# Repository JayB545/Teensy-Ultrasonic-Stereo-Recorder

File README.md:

# TUFR 4.2 - Teensy Ultrasonic Field Recorder

Firmware 4.2, build 2026-11-14b.

Low-power field recorder for ultrasonic sound (bats, cetaceans). A Teensy 4.1 records 16-bit WAV or lossless FLAC files to a microSD card from a WMXZ-EU ADC_V2 module (TLV320ADC6140): 1, 2 or 4 channels at 48/96/192 kHz, 1-2 channels at 384 kHz, 1 channel at 768 kHz or `-768` (768 kHz sampled, 384 kHz files). Every deployment setting is read from `TUFR_Setup.txt` on the SD card; nothing needs recompiling.

**Users: see the TUFR 4.2 User Manual** for the setup file, filter responses, gain, file formats, scheduling, LED codes and the log. This README is for whoever builds or modifies the firmware.

## Building

- Arduino IDE with Teensyduino, board **Teensy 4.1**, Tools > Optimize **"Faster"**.
- Libraries: **SdFat** (the Teensyduino copy), **Time** (TimeLib), **Wire**. No Snooze library.
- The sketch folder must be named `TUFR_4.2` (Arduino requires the folder to match `TUFR_4.2.ino`).
- RAM: the FLAC encoder reserves about 92 KB of RAM1 even in WAV mode. If the compile reports RAM1 short, build `tufr_flac.c` with `-DTUFR_FLAC_MAX_BLOCK=1024` (files about 0.3 % larger).
- Uploading with the Teensy Loader sets the RTC to the computer's clock.
- Before a field release check that `TUFR_WDT_TEST` is `0`.

## Hardware notes

- MotherBoard: BarlowAGAD TUFR Bridgeboard v3a (the v4 motherboard is in design). Pin assignments are in `TUFR_Config.h` and `TUFR_pin_table.html`: ADC_EN 9, SHDNZ 6, I2C SDA 18 / SCL 19, BCLK 21, LRCLK 20, data 8, shutdown button 2, LED 13, Vin divider 22 (A8). In the current version, components are hand-soldered onto the bare motherboard.
- ADC Module: In the current version, the ADC module is manufactured fully populated (except for the pin headers).
- **IOVD**: the ADC module's IOVD pad must be connected to the Teensy 3.3 V (without it: cold-start dropouts at 384 kHz and HF spikes).
- **USB power**: cut the Teensy's VUSB-VIN pad. USB then carries data only; bench work with the serial monitor needs battery or bench-supply power. `Vin` in the log is then the buck output (about 4.1 V); below about 3.8 V the batteries are running out.
- Input pins must stay within the ADC's supply rails (0 to 3.3 V). Consider a series resistor and clamp diodes per input if a pre-amp runs from a higher supply.

## Compile-time settings

| Setting | Where | Default | What it does |
| --- | --- | --- | --- |
| `TUFR_WATCHDOG` | `TUFR_4.2.ino` | 1 | Hardware watchdog (RTWDOG) on |
| `WDT_TIMEOUT_S` | `TUFR_4.2.ino` | 10 | Watchdog timeout, seconds (bench-confirmed) |
| `TUFR_WDT_TEST` | `TUFR_4.2.ino` | 0 | Bench test: 1 = stop feeding the watchdog 30 s into the first file (runs once; delete `TUFR_WDT_DONE.TXT` to repeat). **0 for the field.** |
| `DEAD_STREAM_RECOVER_MS` | `TUFR_4.2.ino` | 500 | All-zero audio this long = dead stream |
| `DEAD_STREAM_INPLACE_TRIES` | `TUFR_4.2.ino` | 3 | In-place ADC restarts per file before a full power cycle |
| `POWER_CYCLE_SHORT_S`, `_LONG_S`, `_SHORT_TRIES` | `TUFR_4.2.ino` | 60, 600, 3 | Power-off time for recovery: 60 s, then 10 min after three in a row |
| `SD_WRITE_FAIL_RUN` | `TUFR_4.2.ino` | 8 | Consecutive failed SD writes that count as a failing card |
| `TUFR_PREALLOCATE` | `TUFR_4.2.ino` | 0 | Preallocate the next file (off: preallocation caused mid-file misses) |
| `TUFR_USB_OFF` | `TUFR_4.2.ino` | 2 | Power down USB PHY and PLL while recording if no serial monitor is open (saves about 13 mA) |
| `gFiltSel` | `TUFR_4.2.ino` | -1 | ADC decimation filter: -1 auto (linear phase at 384 kHz, ultra-low latency elsewhere), 0 linear, 1 low latency, 2 ultra-low latency. Not in the setup file. |
| `TUFR_HPF_D1_SIGN` | `TUFR_Config.h` | 1 | Sign convention of the programmable high-pass (1 is correct) |
| `TUFR_VIN_DIVIDER` | `TUFR_Config.h` | 2.0 | (Rtop + Rbottom) / Rbottom of the Vin divider on pin 22 |
| `TUFR_FLAC_MAX_BLOCK` | `tufr_flac.h` | 2048 | FLAC frame length per channel |
| `MAX_QUEUE` | `global.h` | 14 | Audio queue, 32 KB slots (about 300 ms at 384 kHz x 2 ch) |

## How it works

- **Capture**: Walter Zimmer's SAI/DMA driver fills a 14-slot queue of 16-bit samples (32 KB per slot); `loop()` writes slots to the card, or encodes them to FLAC first. In `-768` mode a 43-tap half-band FIR in the DMA interrupt halves the rate.
- **Gap-free files**: in continuous mode the next file is opened about 6 s before the join, so only the old file's close (about 25 ms) falls at the join; each file starts at the previous file's scheduled end, so files are exactly the set length. The FLAC encoder carries its state across files.
- **FLAC** (`tufr_flac.c/.h`, written for TUFR, no libFLAC, no malloc): fixed predictors of order 0-4 chosen per channel per frame, partitioned Rice coding (up to 64 partitions), 2048-sample frames, constant/verbatim subframes, a 512-byte header so every 32 KB SD write stays sector-aligned, header rewritten at close. About 33 cycles per sample on quiet input, 40-48 on loud input.
- **Waits** (duty cycle, daily window, scheduled start) use Walter Zimmer's SNVS hibernate: the 3.3 V regulator is switched off (0.75 mA) and the RTC alarm restarts the board; a marker file `TUFR_HIB.TXT` tells the restart it is a wake.
- **Unattended recovery**: nothing but the shutdown button stops the recorder for good.
  1. Dead stream (0.5 s of zeros): up to 3 in-place ADC restarts per file, pauses 0.3, 2 and 10 s.
  2. Full power cycle (hibernate 60 s, then 10 min after three in a row; count reset after a file with 10 s of live audio) when that fails, when the ADC does not answer (5 blinks), or on any SD problem (2 blinks: missing, full, failing writes, file not created). Hibernation also removes IOVD power, which an in-place ADC restart cannot.
  3. Watchdog: a hang of 10 s restarts the chip, which powers off at once (before touching the SD card) for 60-123 s. The wake time is chosen so that the alarm second modulo 64 is 37; the next boot recognises that and logs `WATCHDOG_RESET`. (The SNVS general-purpose registers did not keep a value through the power-off on this board, so they are not used.)
- **SD space**: free space is measured once per boot (`SD_SPACE`) and counted down as files close; a file is started only if a full-size WAV file would fit.
- **Setup file**: ten lines in a fixed order; the file-format line is a word (`WAV`/`FLAC`); if line 4 is a number the format line is treated as missing (WAV). 3 channels are recorded as 4 (16384-sample blocks are not a whole number of 3-channel frames). `-768` with FLAC raises the clock to 100 MHz.

## Files

| File | Role |
| --- | --- |
| `TUFR_4.2.ino` | Main sketch: setup file, file handling, FLAC staging, waits, hibernate, recovery, watchdog |
| `tufr_flac.c/.h` | Lossless FLAC encoder |
| `Teensy.cpp/.h`, `adc.cpp/.h`, `process.h`, `queueProcess.cpp`, `global.h` | Walter Zimmer's capture driver (modifications noted in the sketch header) |
| `adcRuntime.cpp/.h` | ADC configuration, channel count, high-pass, retries, health checks |
| `rtc.h`, `rtcImpl.cpp` | Time functions for the capture driver (never define `rtc_get`/`rtc_set` here; they belong to the Teensy core) |
| `TUFR_Config.h` | Pins, Vin divider, high-pass sign |
| `TUFR_Setup.txt` | Template setup file for the SD card |
| `TUFR_pin_table.html` | Printable pin table |

The PC test harness for the encoder (`TUFR_flac_pc_test`) ships beside this folder.

## Status (2026-11-14)

Bench-validated on Bridgeboard v3:

- WAV and FLAC at 384 kHz x 1 and 2 ch, 192 kHz x 4 ch, `-768`; continuous files joined without gaps; 60 MHz with no mid-file misses, including loud white noise on all channels (worst case 62 % CPU).
- High-pass presets and programmable corners; frequency response at 96, 192, 384 kHz and `-768` (see the manual).
- Setup file 13b format, 3 to 4 channels, `CLOCK_RAISED`.
- Recovery: watchdog restart, power-off and `WATCHDOG_RESET` logging; missing SD card (2 blinks, recording resumes when a card is inserted).
- Hibernate between recordings at 0.75 mA; recording 87 mA at 384 kHz x 2 ch WAV.

### Bench tests still to do

1. Full card: a nearly full card should end with complete files, `CARD_FULL` and 2 blinks.
2. A WAV file cut off by a reset should open in Audacity and PAMGuard (placeholder header "length unknown").
3. Recording current, FLAC vs WAV at 60 MHz and at other rates and channel counts (the manual's battery figures cover only 384 kHz x 2 ch WAV).
4. One recording on the towed array with the 40 dB pre-amp and about 10 dB ADC gain: headroom and FLAC ratio.
5. Recording at 48 kHz (anti-alias response not measured).

### Known open issues

- An input overload (1.5 Vrms) once stopped the ADC's output entirely (seen twice on 2026-11-13, not reproduced since); recovery now covers it.
- Small spikes at 468 Hz and multiples (source unknown), a 32.77 kHz spur (RTC crystal), 60 Hz pickup.
- The first file of a 768 kHz run can lose up to about 1 s to an SD stall at start-up (before the file opens).

## Version history

- **4.2 (2026-11-12 to 11-14)**: optional FLAC; encoder 3x faster (13a); setup file reordered with the format as a word, decimation-filter line removed (13b); 3 channels recorded as 4, `-768` + FLAC at 100 MHz (13c); unattended recovery and watchdog (13d); SD-card checks (14a); watchdog wake recognised by its alarm time (14b).
- **4.1 (2026-11-03 to 11-09)**: Walter Zimmer's capture driver; ADC protection; SNVS hibernate; daily window and scheduled start; gap-free continuous files; programmable high-pass; `-768` decimation; Vin logging; USB power-down while recording.
- **4.0**: first version with its own SAI capture (garbled at 384 kHz x 2 ch).

Credits: capture driver and hibernate method (c) Walter Zimmer, microPAM project (https://github.com/WMXZ-EU/LC-MARE/tree/main/microPAM_V3); ADC configuration sequence from his `adc.cxx`. Adapted by Jay Barlow with Claude (Anthropic).

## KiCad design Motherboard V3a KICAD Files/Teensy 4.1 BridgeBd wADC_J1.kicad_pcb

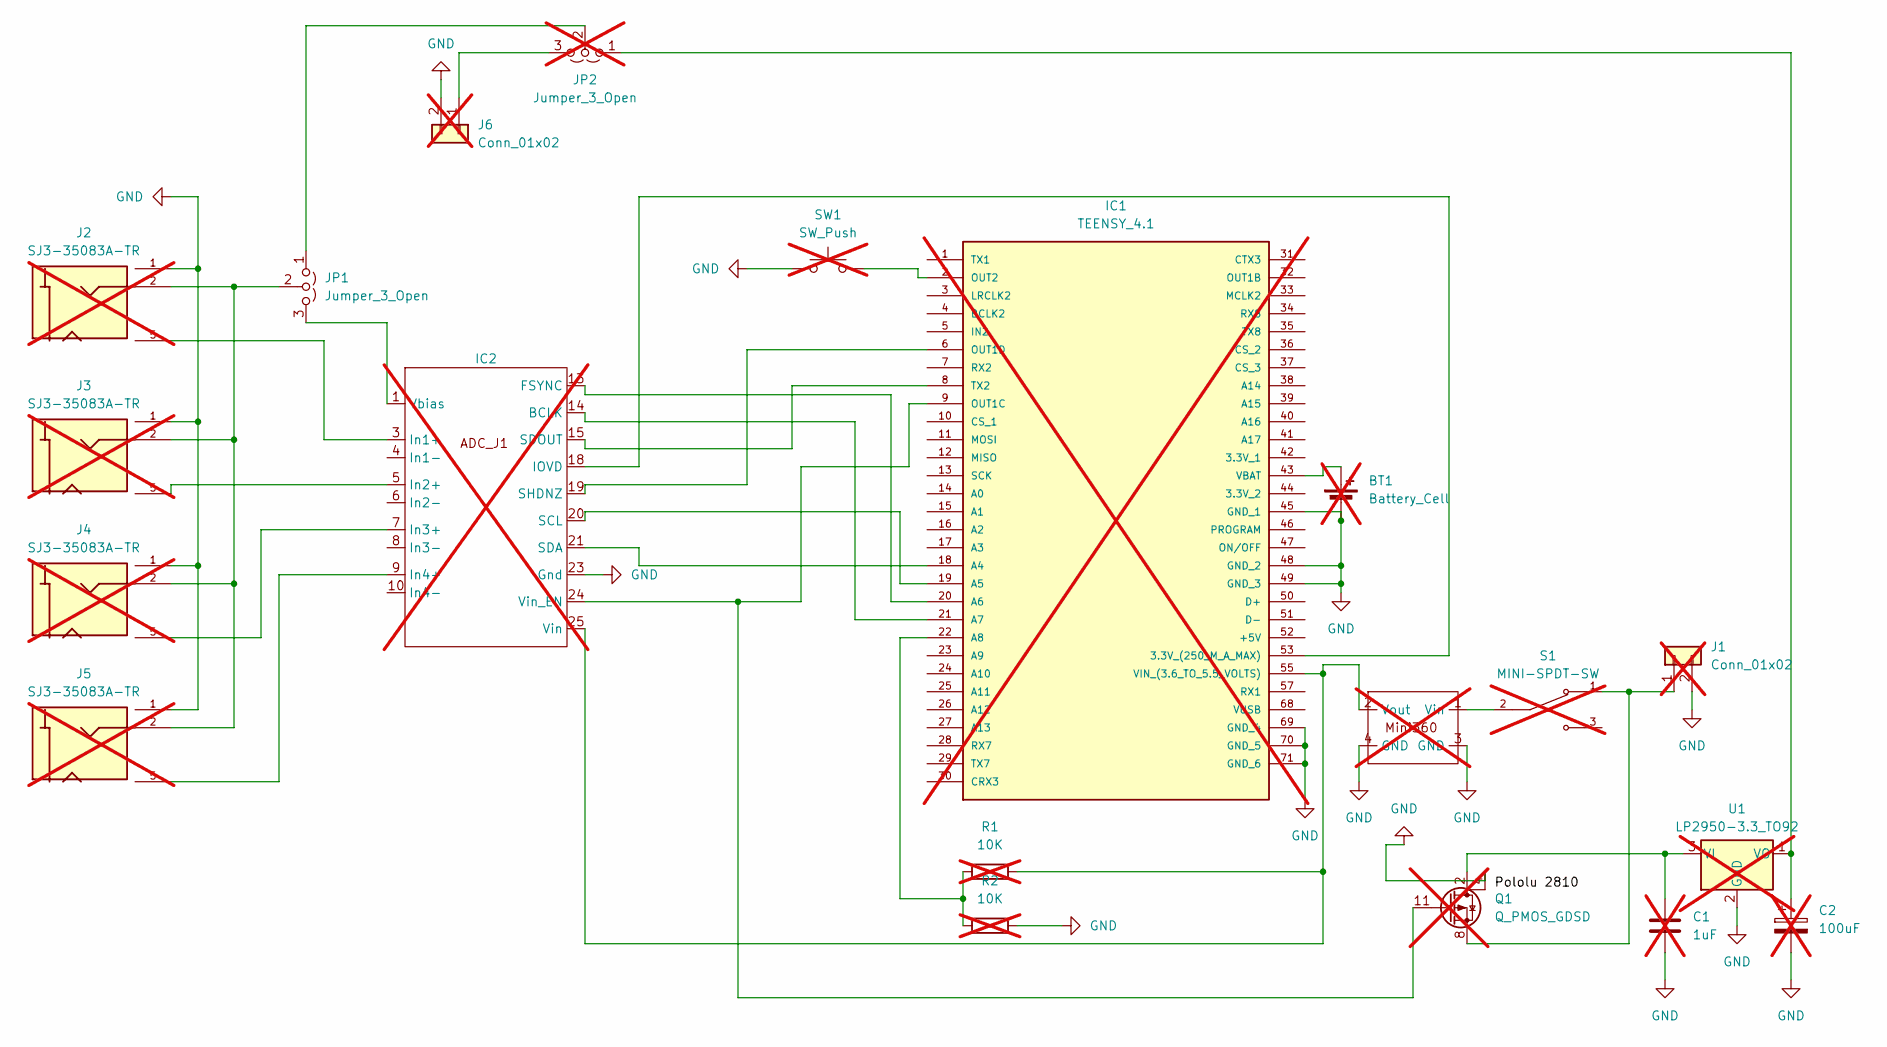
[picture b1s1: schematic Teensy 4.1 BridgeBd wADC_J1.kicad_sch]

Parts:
BT1: Battery_Cell; BatteryHolder_Keystone_103_1x20mm; not fitted
C1: 1uF; C_Disc_D3.4mm_W2.1mm_P2.50mm; not fitted
C2: 100uF; CP_Radial_D5.0mm_P2.50mm; not fitted
IC1: TEENSY_4.1; TEENSY41; Manufacturer_Part_Number TEENSY 4.1; not fitted
IC2: ADC_J1 Footprint; not fitted
J1, J6: Conn_01x02; Vin Conn; not fitted
J2, J3, J4, J5: SJ3-35083A-TR; SAMESKY_SJ3-35083A-TR; PARTREV 1.01; not fitted
JP1: Jumper_3_Open; PinHeader_1x03_P2.54mm_Vertical
JP2: Jumper_3_Open; PinHeader_1x03_P2.54mm_Vertical; not fitted
Mini1: Mini360 Buck; not fitted
Q1: Q_PMOS_GDSD; Pololu 2810 switch; not fitted
R1, R2: 10K; R_Axial_DIN0207_L6.3mm_D2.5mm_P5.08mm_Vertical; not fitted
S1: MINI-SPDT-SW; SW_MINI-SPDT-SW; PARTREV C; not fitted
SW1: SW_Push; ShutDownSwitch; not fitted
U1: LP2950-3.3_TO92; TO-92_Inline_Wide; not fitted

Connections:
GND: BT1.2 (-), C1.2, C2.2, IC1.45 (GND_1), IC1.48 (GND_2), IC1.49 (GND_3), IC1.69 (GND_4), IC1.70 (GND_5), IC1.71 (GND_6), IC2.23 (Gnd), J1.2, J2.1, J3.1, J4.1, J5.1, J6.2, Mini1.3 (GND), Mini1.4 (GND), Q1.4 (D), R2.1, SW1.1 (Gnd), U1.2 (GND)
unnamed: BT1.1 (+), IC1.43 (VBAT)
unnamed: IC1.53 (3.3V_(250_M_A_MAX)), IC2.18 (IOVD)
unnamed: IC1.18 (A4), IC2.21 (SDA)
unnamed: IC1.19 (A5), IC2.20 (SCL)
unnamed: IC1.20 (A6), IC2.13 (FSYNC)
unnamed: IC1.21 (A7), IC2.14 (BCLK)
unnamed: IC1.22 (A8), R1.2, R2.2
unnamed: IC1.9 (OUT1C), IC2.24 (Vin_EN), Q1.11 (G)
unnamed: IC1.6 (OUT1D), IC2.19 (SHDNZ)
unnamed: IC1.2 (OUT2), SW1.2 (Ctrl)
unnamed: IC1.8 (TX2), IC2.15 (SDOUT)
unnamed: IC1.55 (VIN_(3.6_TO_5.5_VOLTS)), IC2.25 (Vin), Mini1.2 (Vout), R1.1
unnamed: IC2.3 (In1+), J2.5
unnamed: IC2.5 (In2+), J3.5
unnamed: IC2.7 (In3+), J4.5
unnamed: IC2.9 (In4+), J5.5
unnamed: IC2.1 (Vbias), JP1.3 (B)
unnamed: J1.1, Q1.8 (S), S1.1
unnamed: J6.1, JP2.3 (B)
unnamed: JP1.1 (A), JP2.2 (C)
unnamed: J2.2, J3.2, J4.2, J5.2, JP1.2 (C)
unnamed: C2.1, JP2.1 (A), U1.1 (VO)
unnamed: Mini1.1 (Vin), S1.2
unnamed: C1.1, Q1.2 (D), U1.3 (VI)

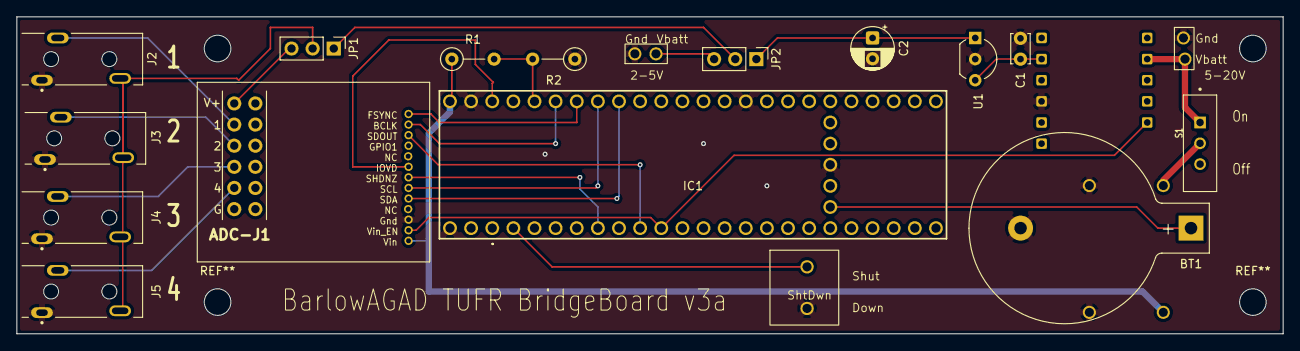
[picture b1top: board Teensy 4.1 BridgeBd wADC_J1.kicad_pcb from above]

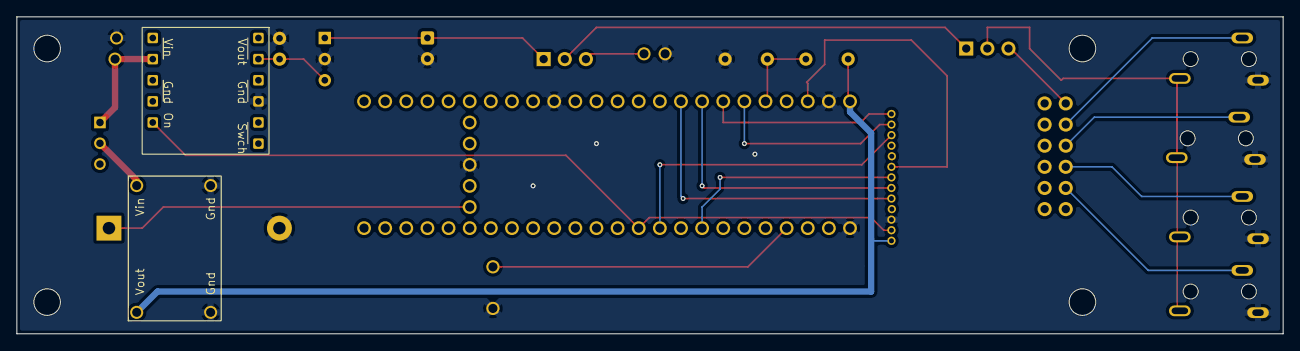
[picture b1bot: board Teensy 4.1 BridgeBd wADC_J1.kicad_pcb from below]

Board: 4 copper layers, 152.2 x 38.1 mm, 20 parts (2 on the bottom side), 25 nets.

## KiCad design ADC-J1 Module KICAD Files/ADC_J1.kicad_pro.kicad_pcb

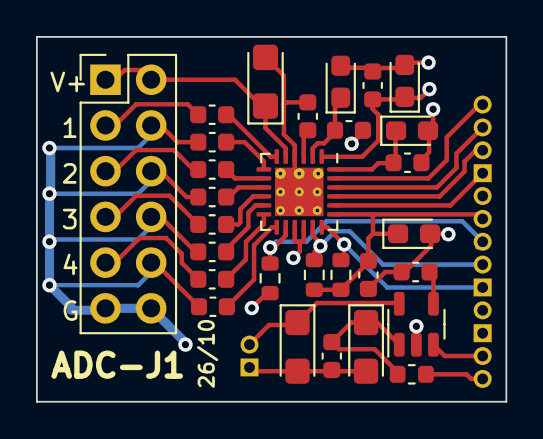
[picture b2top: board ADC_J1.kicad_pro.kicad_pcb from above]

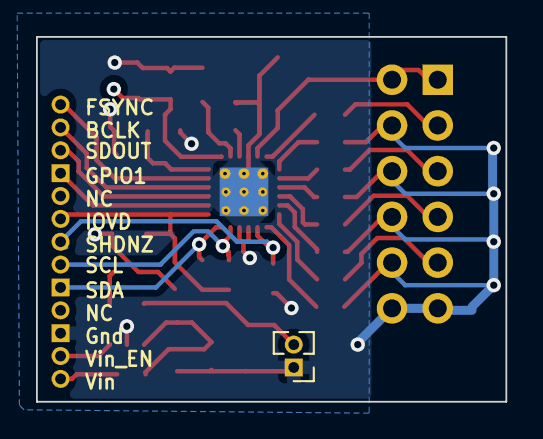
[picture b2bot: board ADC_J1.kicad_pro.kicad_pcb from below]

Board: 4 copper layers, 26.1 x 20.3 mm, 33 parts (4 on the bottom side), 30 nets.

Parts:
C1, C25: 47u; CP_EIA-3216-12_Kemet-S
C2, C3, C4, C5, C6, C7, C12, C18, C19: 1u; C_0603_1608Metric
C11: 100u; CP_EIA-3216-10_Kemet-I
C13, C14, C30: 10u; CP_EIA-2012-15_AVX-P
C15, C16, C20, C23, C27, C29: 0.1u; C_0603_1608Metric
C21: 1u; CP_EIA-2012-15_AVX-P
J1: Conn_01x12_Pin; PinHeader_2x06_P2.54mm_Vertical
J3: Conn_01x03; PinHeader_1x03_P1.27mm_Vertical
J6, J7: Conn_01x04; PinHeader_1x04_P1.27mm_Vertical
J9: Conn_01x02_Pin; PinHeader_1x02_P1.27mm_Vertical
L1: BLM18HG601SN1D; L_0603_1608Metric
R15, R16, R18: 10k; R_0603_1608Metric
U3: TLV320ADC6140; QFN-24-1EP_4x4mm_P0.5mm_EP2.7x2.7mm_ThermalVias
U4: MIC5219-3.3YM5; SOT-23-5

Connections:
/AVDD: C20.1, C21.1, C25.1, J9.2, U3.1 (AVDD), U4.5 (OUT)
/BCLK: J6.3, U3.22 (BCLK)
/FSYNC: J6.4, U3.23 (FSYNC)
/GPIO1: J6.1, U3.20 (GPIO1)
/IOVD: C29.1, C30.1, J7.4, R15.1, R18.1, U3.19 (IOVD)
/MicBias: C11.1, J1.1, J1.2, U3.5 (MICBIAS)
/SCL: J7.2, R15.2, U3.17 (SCL_MOSI)
/SDA: J7.1, R18.2, U3.18 (SDA_SSZ)
/SDOUT: J6.2, U3.21 (SDOUT)
/SHDNZ: J7.3, R16.2, U3.14 (SHDNZ)
/VIN: C1.1, C27.2, L1.1, U4.1 (IN)
/VIN_EN: J3.2, U4.3 (EN)
GND: C1.2, C3.2, C5.2, C7.2, C11.2, C12.2, C13.2, C14.2, C15.2, C16.2, C19.2, C20.2, C21.2, C23.1, C25.2, C27.1, C29.2, C30.2, J1.4, J1.6, J1.8, J1.10, J1.11, J1.12, J3.1, J9.1, R16.1, U3.4 (AVSS), U3.15 (ADDR1_MISO), U3.16 (ADDR0_SCLK), U3.25 (PAD), U4.2 (GND)
unnamed: C18.2, J1.3
unnamed: C2.2, J1.5
unnamed: C4.2, J1.7
unnamed: C6.2, J1.9
unnamed: J3.3, L1.2
unnamed: C13.1, C16.1, U3.2 (AREG)
unnamed: C14.1, C15.1, U3.24 (DREG)
unnamed: C19.1, U3.7 (IN1M_GPO1)
unnamed: C18.1, U3.6 (IN1P_GPI1)
unnamed: C3.1, U3.9 (IN2M_GPO2)
unnamed: C2.1, U3.8 (IN2P_GPI2)
unnamed: C5.1, U3.11 (IN3M_GPO3)
unnamed: C4.1, U3.10 (IN3P_GPI3)
unnamed: C7.1, U3.13 (IN4M_GPO4)
unnamed: C6.1, U3.12 (IN4P_GPI4)
unnamed: C12.1, U3.3 (VREF)
unnamed: C23.2, U4.4 (BP)

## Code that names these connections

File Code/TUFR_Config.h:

/*
 * TUFR_Config.h - board wiring and build-time switches for TUFR 4.0
 * (ADC_V2 / TLV320ADC6140 version)
 */
#ifndef TUFR_CONFIG_H
#define TUFR_CONFIG_H

// Set to 1 to keep USB/serial alive throughout operation, for field
// diagnostics (config readback, overrun counts, SD write timing). Set to
// 0 for lowest power consumption (matches TUFR 2.4's default behavior).
#ifndef TUFR_DEBUG_SERIAL
#define TUFR_DEBUG_SERIAL 1
#endif

// Programmable high-pass filter (setup line 5): sign of the D1 coefficient. The
// datasheet's transfer function was not available, so +1 is an assumption. If a
// custom cutoff gives saturated noise instead of audio, try -1.
#ifndef TUFR_HPF_D1_SIGN
#define TUFR_HPF_D1_SIGN 1
#endif

// ---- Pins carried over unchanged from TUFR 2.4 ----
#define PIN_LED         13
#define PIN_SHUTDOWN    2
#define PIN_BATT        A8   // = pin 22, mid-point of the battery-voltage divider

// Vin sense: the divider on PIN_BATT is read and logged as "Vin = x.xx" (volts at the
// board's supply input) with CONFIG and with every file's stats line, so an unplanned
// stop from a depleted battery shows up as a falling Vin in TUFR_log.txt.
// TUFR_VIN_DIVIDER = (Rtop + Rbottom) / Rbottom: 2.0 for two equal resistors (10k/10k).
// The pin must never see more than 3.3 V, so a 1:1 divider measures at most 6.6 V.
// For the 5-20 V input of the planned buck board use a ratio of about 7 (e.g. 10k over
// 1.8k, ratio 6.56 -> 21.6 V full scale) and set this to the real value.
#ifndef TUFR_VIN_DIVIDER
#define TUFR_VIN_DIVIDER 2.0f
#endif

// ---- ADC_V2 / TLV320ADC6140 control pins ----
// PIN_ADC_EN drives the board's VIN_EN (onboard 3.3V LDO enable) - this is
// the same physical pin (9) that previously drove the Pololu switch.
// PIN_ADC_SHDNZ drives SHDNZ (the ADC6140's own reset/shutdown pin) and is
// new - the WM8782 had no equivalent.
#define PIN_ADC_EN      9
#define PIN_ADC_SHDNZ   6

// ---- I2S (SAI1) pins - unchanged from TUFR 2.4's wiring ----
// These are fixed by the Teensy 4.1's SAI1 peripheral pinout, not
// arbitrary GPIOs, so they cannot be moved without also changing the
// register setup in saiCapture.cpp.
#define PIN_I2S_BCLK    21   // SAI1_RX_BCLK  (Teensy drives this - master)
#define PIN_I2S_LRCLK   20   // SAI1_RX_SYNC  (Teensy drives this - master)
#define PIN_I2S_DATA     8   // SAI1_RX_DATA0 (from ADC SDOUT)

// ---- I2C (ADC configuration bus) ----
// Uses the default `Wire` (pins 18/19), matching mWire=Wire in Walter's
// global.h for the T_4_1 target.

#endif
